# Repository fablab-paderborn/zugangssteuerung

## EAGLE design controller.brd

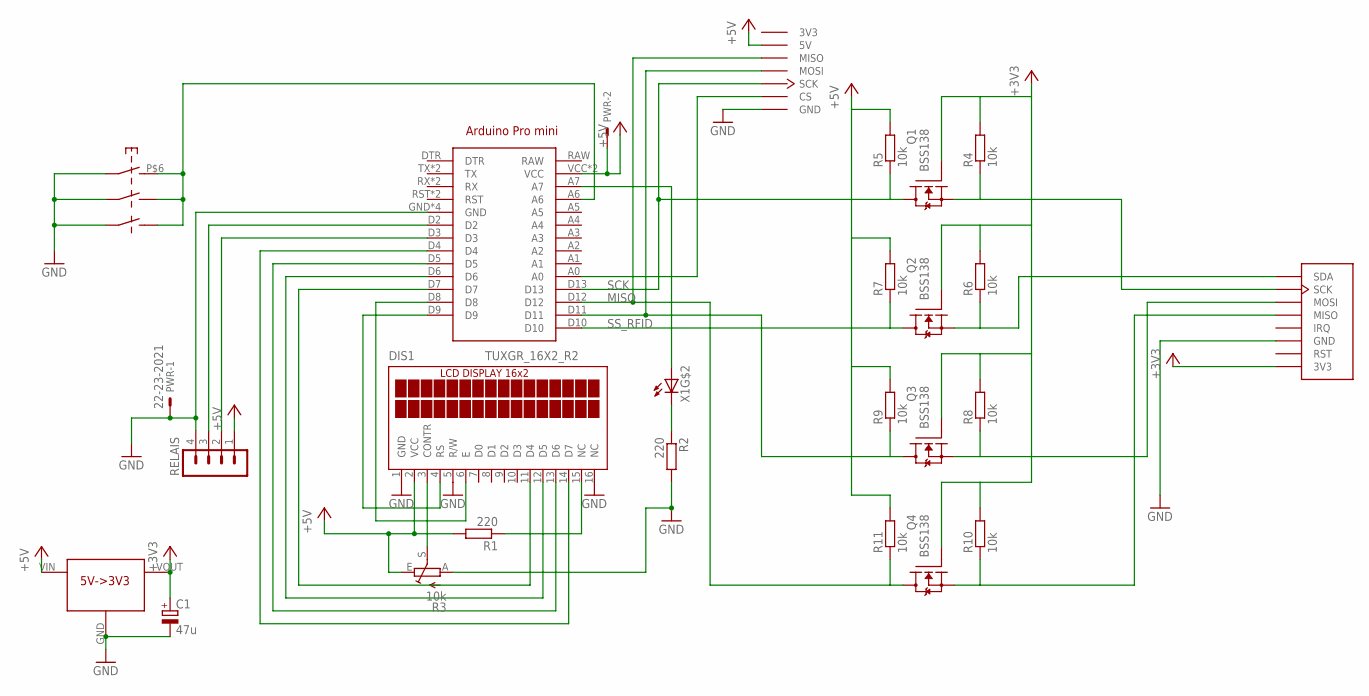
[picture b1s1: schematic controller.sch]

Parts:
ARDUINO1: ARDUINO_PRO_MINI
C1: 47u; B45181B
DIS1: TUXGR_16X2_R2
PWR: 22-23-2021
Q1, Q2, Q3, Q4: BSS138; SOT23
R1, R2: 220; R0805
R3: 10k; CA9V
R4, R5, R6, R7, R8, R9, R10, R11: 10k; R0805
RELAIS: MA04-1
U$1: SD_CARD
U$3: RFID-RC522; BOARD
U$4: PWR_CONV
X1: PUSHBUTTON_LED

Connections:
3V3: U$1.P$3V3 (3V3), U$1.P$3V3_2 (3V3)
+3V3: C1.+, Q1.1 (G), Q2.1 (G), Q3.1 (G), Q4.1 (G), R4.2, R6.2, R8.2, R10.2, U$3.3V3, U$4.VOUT
+5V: ARDUINO1.VCC, ARDUINO1.VCC@1 (VCC), DIS1.2 (VCC), PWR.2, R1.2, R3.E, R5.2, R7.2, R9.2, R11.2, RELAIS.1, U$1.P$5V (5V), U$1.P$5V_2 (5V), U$4.VIN
GND: ARDUINO1.GND, ARDUINO1.GND@1 (GND), ARDUINO1.GND@2 (GND), ARDUINO1.GND@3 (GND), C1.-, DIS1.1 (GND), DIS1.5 (R/W), DIS1.16 (NC), PWR.1, R2.2, R3.A, RELAIS.4, U$1.GND, U$1.GND$2 (GND), U$1.GND$3 (GND), U$1.GND$4 (GND), U$3.GND, U$4.GND, X1.P$1 (1), X1.P$3 (3), X1.P$5 (5)
MISO: ARDUINO1.D12, Q4.3 (D), R11.1, U$1.P$MISO (MISO), U$1.P$MISO2 (MISO)
MOSI: ARDUINO1.D11, Q3.3 (D), R9.1, U$1.P$MOSI (MOSI), U$1.P$MOSI2 (MOSI)
unnamed: R2.1, X1.P$C (C)
unnamed: Q1.2 (S), R4.1, U$3.SCK
unnamed: Q3.2 (S), R8.1, U$3.MOSI
unnamed: Q4.2 (S), R10.1, U$3.MISO
unnamed: ARDUINO1.A0, U$1.P$CS (CS), U$1.P$CS2 (CS)
unnamed: ARDUINO1.D5, DIS1.13 (D6)
unnamed: DIS1.3 (CONTR), R3.S
unnamed: ARDUINO1.D7, DIS1.11 (D4)
unnamed: ARDUINO1.A7, X1.P$A (A)
unnamed: ARDUINO1.D8, DIS1.6 (E)
unnamed: ARDUINO1.D9, DIS1.4 (RS)
unnamed: ARDUINO1.D6, DIS1.12 (D5)
unnamed: ARDUINO1.D3, RELAIS.2
unnamed: ARDUINO1.D2, RELAIS.3
unnamed: ARDUINO1.A6, X1.P$2 (2), X1.P$4 (4), X1.P$6 (6)
unnamed: DIS1.15 (NC), R1.1
unnamed: ARDUINO1.D4, DIS1.14 (D7)
SCK: ARDUINO1.D13, Q1.3 (D), R5.1, U$1.P$SCK (SCK), U$1.P$SCK2 (SCK)
SS_RFID: ARDUINO1.D10, Q2.3 (D), R7.1
SS_RFID_3V3: Q2.2 (S), R6.1, U$3.SDA

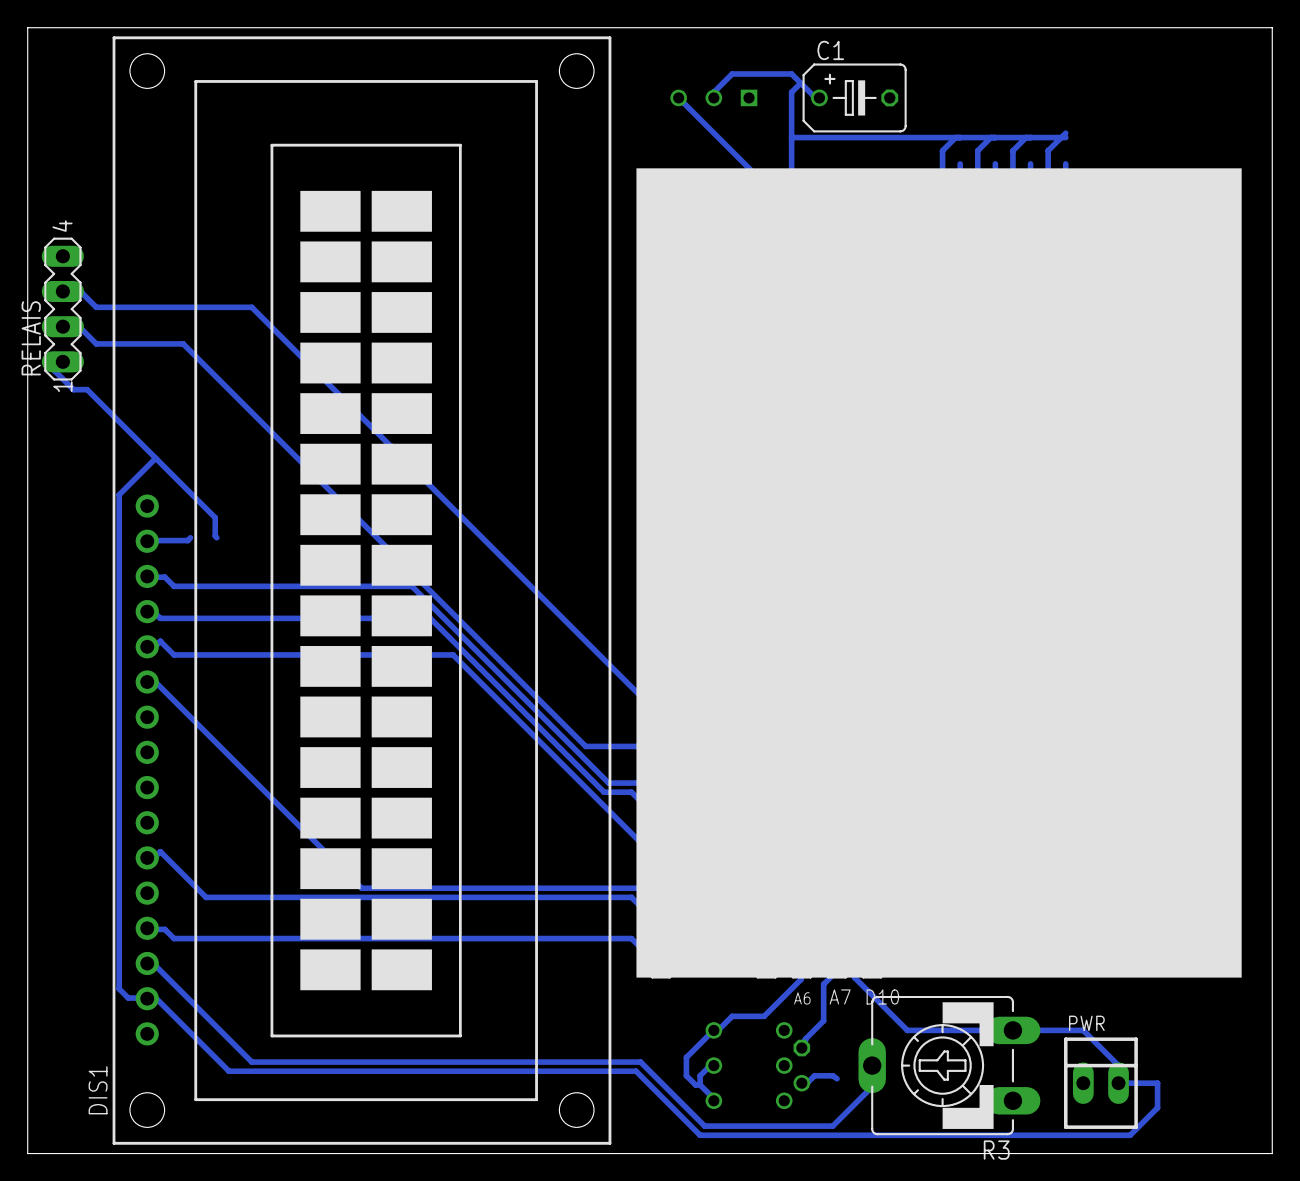
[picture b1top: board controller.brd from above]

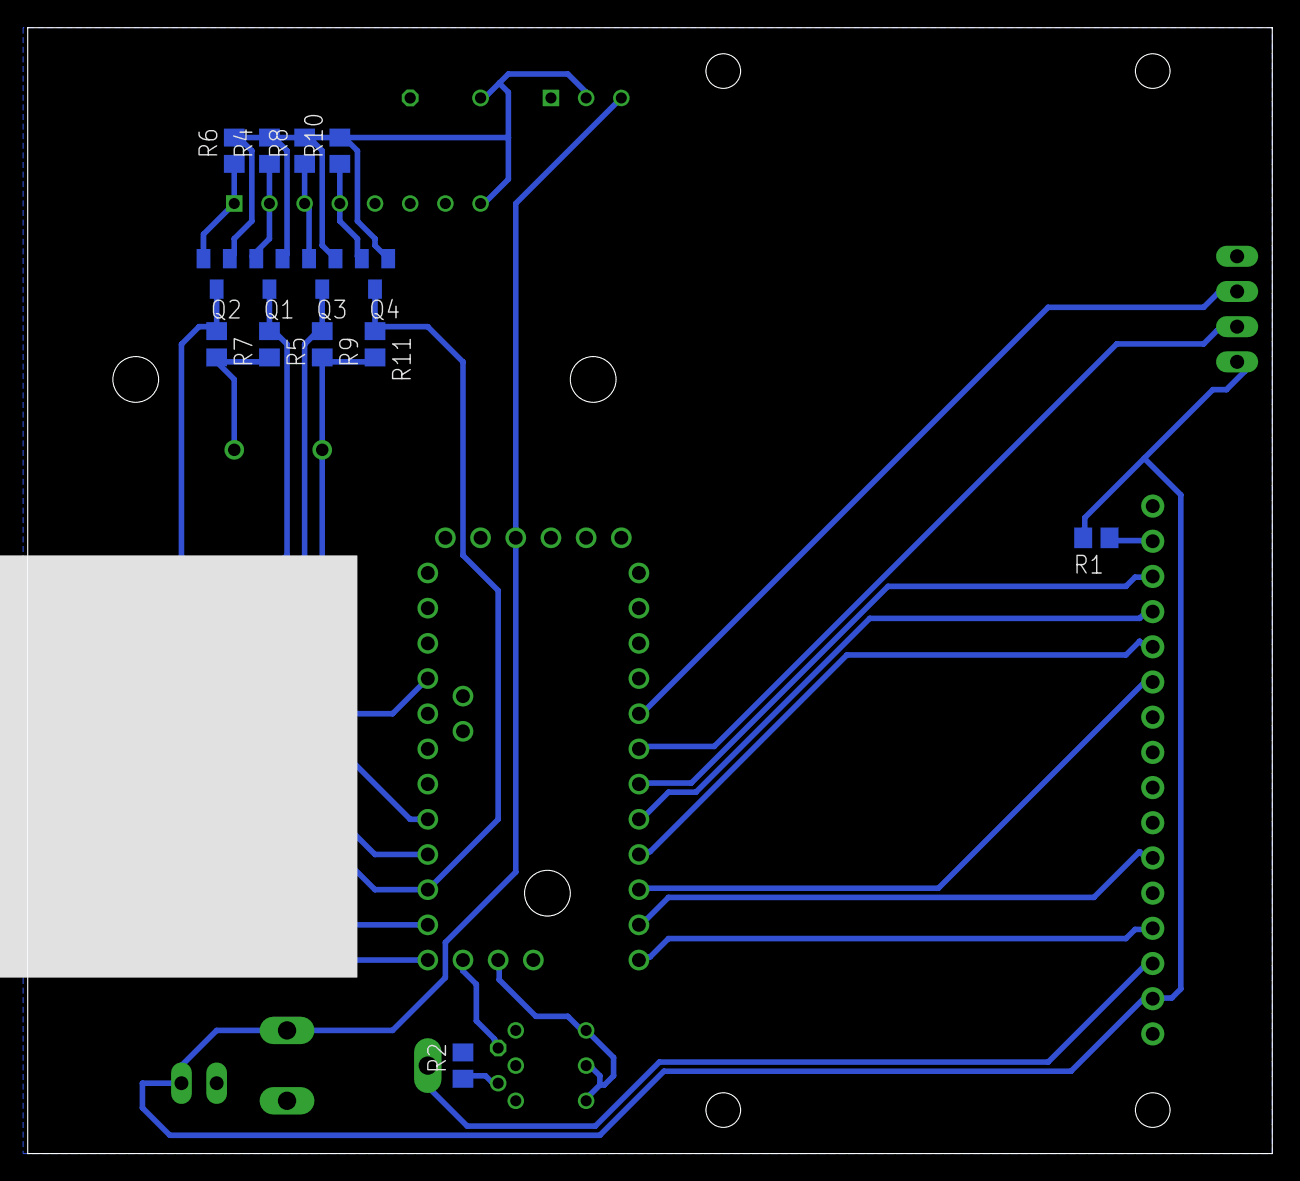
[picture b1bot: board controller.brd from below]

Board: 2 copper layers, 89.8 x 81.3 mm, 24 parts (15 on the bottom side), 26 nets.

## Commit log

2015-07-14 starts to work
2015-07-14 umbenennung
2015-07-14 nicer logging
2015-07-24 let cooling run longer, and write log file entries every 5 minutes
2015-09-12 board draft
2015-12-31 board layout, should work
